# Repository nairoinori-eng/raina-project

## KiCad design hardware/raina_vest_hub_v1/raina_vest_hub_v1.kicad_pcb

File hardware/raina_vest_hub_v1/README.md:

# RAINA 背心中转控制板 v1.0（不推荐下单）

> 重要：v1 的 Arduino Nano 直插封装来自手写坐标，导入嘉立创EDA后存在封装和引脚可靠性风险。不要直接用 v1 下单。
>
> 推荐改用 `hardware/raina_vest_hub_v2_terminal`：Arduino Nano 不直接插板，而是通过 8P 线连接到中转板，PCB 上只保留传感器分压和马达驱动，风险更低。

这是一块用于替代面包板的 Arduino Nano 扩展 PCB 方案。目标是把电阻、三极管、接口全部固定到一块小板上，背心内只保留 FSR 压力传感器、振动马达和延长线。

## 0. 可直接打开的 PCB 文件

本目录已经包含一套 KiCad PCB 工程：

- `raina_vest_hub_v1.kicad_pro`
- `raina_vest_hub_v1.kicad_pcb`
- `raina_vest_hub_v1.easyeda.json`

使用方法：

1. 安装 KiCad。
2. 打开 `raina_vest_hub_v1.kicad_pro`。
3. 进入 PCB 编辑器检查板子。
4. 核对 S9012 实物脚位、Arduino Nano 插入方向、JST 插座方向。
5. 没问题后导出 Gerber，再上传嘉立创打样。

注意：这版是为了毕业设计快速落地做的手工布线小板，不是工业量产板。下单前必须人工检查 DRC，尤其是 S9012 脚位。

Nano 插座按 USB 朝上校准：

- A0/A1/A2/A3 在左排第 4/5/6/7 脚。
- 5V 在左排第 12 脚。
- GND 在左排第 14 脚。
- D5 在右排第 8 脚。
- D6 在右排第 9 脚。

如果你导入后看到 D5/D6 不在这两个位置，不要下单。

如果你使用嘉立创EDA标准版，可以直接导入 `raina_vest_hub_v1.easyeda.json`：

1. 打开嘉立创EDA标准版。
2. 选择“文件 / 导入 / EasyEDA 文件”。
3. 选择 `raina_vest_hub_v1.easyeda.json`。
4. 打开后先运行 DRC，再检查接口方向和 S9012 脚位。

## 1. 默认假设

- 主控：Arduino Nano，使用排针插到 PCB 上。
- 传感器接口：JST-XH 2P，间距 2.54mm。
- 马达接口：JST-XH 2P，间距 2.54mm。
- 电阻：直插 1/4W，间距 7.62mm。
- 三极管：S9012，TO-92 封装。
- 二极管：1N4148 / 1N4007 / 1N5819 均可，预留焊盘，正式展出建议焊上。
- PCB：2 层板，1.6mm 厚，FR-4。

## 2. 板上接口

| 接口 | 连接对象 | Arduino 引脚 | 说明 |
|---|---|---|---|
| J1 S1 | 左胸 FSR | A0 | 2P，1脚 5V，2脚信号 |
| J2 S2 | 右胸 FSR | A1 | 2P，1脚 5V，2脚信号 |
| J3 S3 | 左腰 FSR | A2 | 2P，1脚 5V，2脚信号 |
| J4 S4 | 右腰 FSR | A3 | 2P，1脚 5V，2脚信号 |
| J5 M1 | 左胸马达 | D5 | 2P，1脚马达正极，2脚 GND |
| J6 M2 | 右腰马达 | D6 | 2P，1脚马达正极，2脚 GND |

## 3. FSR 传感器电路

每一路都是同样结构：

```text
5V -> FSR -> A0/A1/A2/A3
              |
             10K
              |
             GND
```

PCB 上只放 10K 下拉电阻，FSR 本体通过 JST 线接到背心内部。

## 4. 马达驱动电路

每一路都是 S9012 高边驱动：

```text
D5/D6 -> 1K -> S9012 B
S9012 B -> 10K -> 5V
S9012 E -> 5V
S9012 C -> 马达正极
马达负极 -> GND
```

固件逻辑保持不变：Arduino 输出 LOW 时马达导通，输出 HIGH 时马达关闭。

二极管建议焊在马达两端：

```text
二极管阴极 -> 马达正极
二极管阳极 -> GND
```

## 5. 推荐 PCB 布局

参考 `raina_vest_hub_v1_top_view.svg`。

- Arduino Nano 放中间。
- 左侧放 S1-S4 四个传感器接口。
- 右侧放 M1-M2 两个马达接口。
- 每个接口旁边必须放丝印，避免背心安装时插反。
- 板子四角加 3mm 固定孔，用扎带或螺丝固定到背心外侧小盒子里。

## 6. 嘉立创EDA绘制步骤

1. 新建 2 层 PCB 工程。
2. 放置 Arduino Nano 模块插座，可以用 2 条 15P 排母代替。
3. 放置 6 个 JST-XH-2P 接口。
4. 放置 4 个 10K 下拉电阻，分别连接 A0/A1/A2/A3 到 GND。
5. 放置 2 个 S9012 TO-92、2 个 1K 电阻、2 个 10K 上拉电阻。
6. 每路马达旁预留 1 个二极管焊盘。
7. 按 `netlist.csv` 连线。
8. 铺铜：顶层和底层都铺 GND。
9. 走线建议：5V 和马达线宽 0.5mm 以上，信号线 0.25mm 以上。
10. 下单前用 DRC 检查短路和未连线。

## 7. 背心接线

背心内部每个模块做 JST 2P 插头：

```text
S1 -> J1
S2 -> J2
S3 -> J3
S4 -> J4
M1 -> J5
M2 -> J6
```

线材建议：

- FSR：28AWG 硅胶软线。
- 马达：26AWG 硅胶软线。
- 每根线 60cm 到 100cm，根据背心走线实际裁剪。

## 8. 下单前必须人工确认

- S9012 管脚顺序必须按你手里的实物确认，不同厂家可能不是同一脚位。
- JST 接口 1 脚方向要和线束一致。
- Arduino Nano 排针方向要留出 USB 插头空间。
- 如果马达供电仍用 5V，正式展出前要确认马达不明显发热。

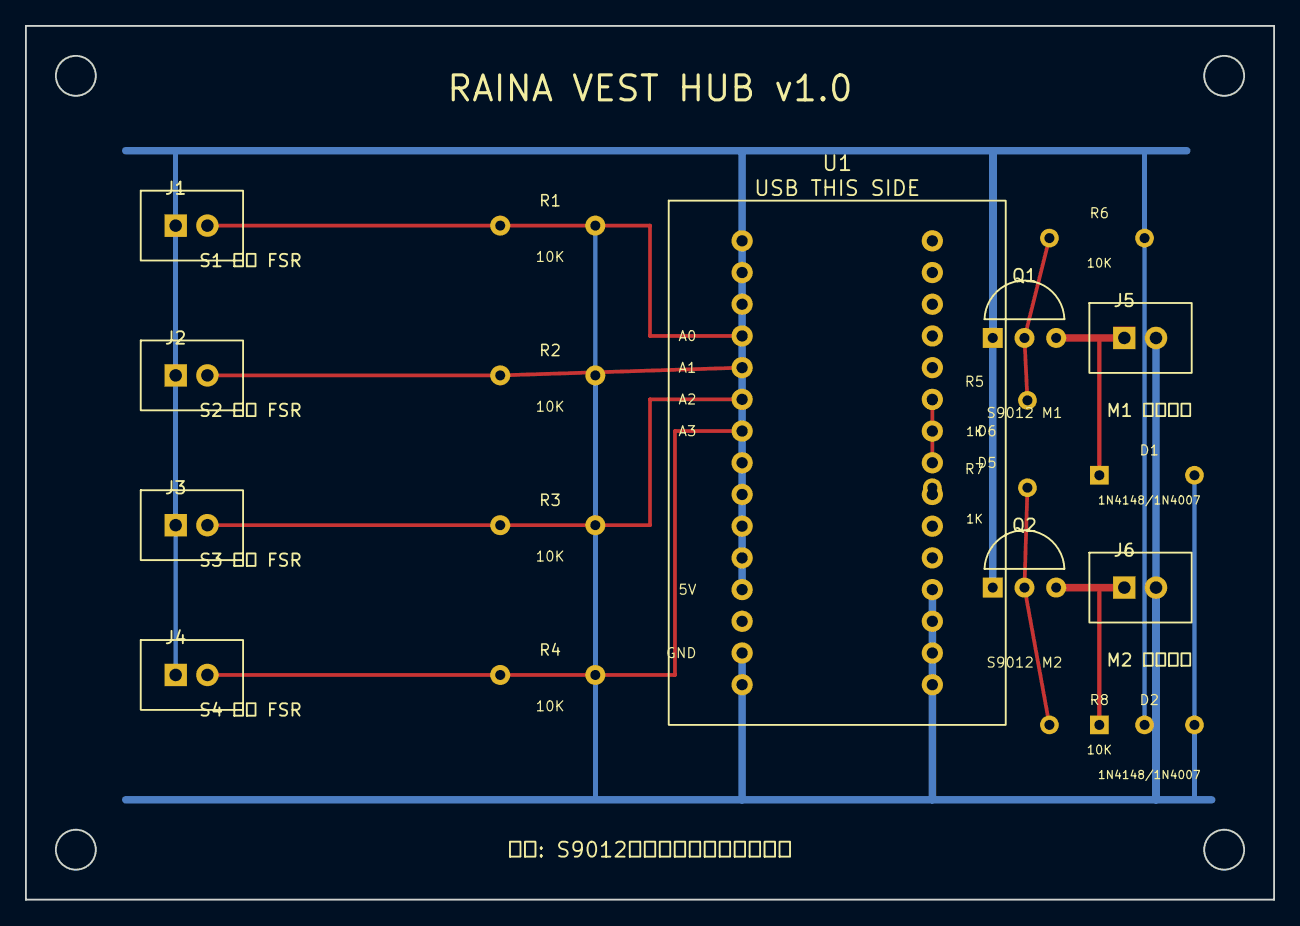
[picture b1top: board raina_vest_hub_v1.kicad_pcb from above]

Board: 2 copper layers, 100.0 x 70.0 mm, 19 parts (0 on the bottom side), 12 nets.

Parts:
D1: 1N4148/1N4007; Diode_D1
D2: 1N4148/1N4007; Diode_D2
J1: S1 左胸 FSR; JST_XH_2P_S1
J2: S2 右胸 FSR; JST_XH_2P_S2
J3: S3 左腰 FSR; JST_XH_2P_S3
J4: S4 右腰 FSR; JST_XH_2P_S4
J5: M1 左胸马达; JST_XH_2P_M1
J6: M2 右腰马达; JST_XH_2P_M2
Q1: S9012 M1; S9012_TO92_Q1
Q2: S9012 M2; S9012_TO92_Q2
R1, R2, R3, R4: 10K; Resistor_THT
R5: 1K; Resistor_R5
R6: 10K; Resistor_R6
R7: 1K; Resistor_R7
R8: 10K; Resistor_R8
U1: Arduino Nano Socket; Arduino_Nano_Socket

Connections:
+5V: J1.1, J2.1, J3.1, J4.1, Q1.E, Q2.E, R6.2, R8.2, U1.L12
GND: D1.A, D2.A, J5.2, J6.2, R1.2, R2.2, R3.2, R4.2, U1.L14, U1.R12
M1_BASE: Q1.B, R5.2, R6.1
M1_CTRL: R5.1, U1.R8
M1_POS: D1.K, J5.1, Q1.C
M2_BASE: Q2.B, R7.2, R8.1
M2_CTRL: R7.1, U1.R9
M2_POS: D2.K, J6.1, Q2.C
S1_SIG: J1.2, R1.1, U1.L4
S2_SIG: J2.2, R2.1, U1.L5
S3_SIG: J3.2, R3.1, U1.L6
S4_SIG: J4.2, R4.1, U1.L7

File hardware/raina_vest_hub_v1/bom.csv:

位号,名称,规格,封装/建议,数量,备注
U1,Arduino Nano 插座,Nano 3.0,2x15P 排母,1,Nano 插在板上
J1-J6,JST 2P 插座,JST-XH 2.54mm 2P,直插,6,S1-S4 和 M1-M2
R1-R4,电阻,10K,直插 1/4W,4,FSR 下拉
R5 R7,电阻,1K,直插 1/4W,2,S9012 基极限流
R6 R8,电阻,10K,直插 1/4W,2,S9012 基极上拉
Q1 Q2,PNP 三极管,S9012 / SS9012,TO-92,2,注意确认脚位
D1 D2,二极管,1N4148/1N4007/1N5819,直插,2,马达保护，建议焊
H1-H4,固定孔,M3,3.2mm 孔,4,固定到外壳或背心

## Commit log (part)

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2026-04-09 fix: 大幅提高藤蔓可见度（alpha/size翻倍，展宽收窄）
    - 主藤alpha: 0.40→0.75, size: 0.028→0.055
    - 径向展宽收窄（0.038→0.022），粒子更集中更实
    - shader基础亮度 0.6→0.8
    - 叶片粒子同步增强
    https://claude.ai/code/session_01WybZpkk4Z2YxGfBpvDxzQV
2026-04-09 feat: 分支藤蔓重写 — 8根手工定义路径，1:1复刻参考图
    逐根追踪参考图中的分支走势，每根用独立CatmullRom曲线：
    1. 顶部左上弯曲延伸
    2. 上部右侧短弧
    3. 左侧长S弧（箭头1位置）
    4. 右侧长S弧（箭头2位置）
    5. 中部左侧中等弧
2026-04-09 chore: 后台agent生成的解析脚本和数据
2026-04-10 feat: 用Figma路径替换正弦藤蔓系统
    - import VINE1_SEGMENTS(15段) 和 VINE2_SEGMENTS(31段) 路径数据
    - CatmullRom插值 + 弧长均匀采样，自动平滑尖锐转折
    - 拓扑分析自动检测主干/分支/末梢，主干粗分支渐细
    - 双态映射：Figma=直立态，curved=加脊柱x偏移
    - Z深度正弦缠绕 + depthFade=0.15 后方变暗
    - 颜色立体感：Z前方偏暖highlight，后方偏冷accent2
2026-04-10 fix: X缩放收回2.0，太宽了
    https://claude.ai/code/session_01WirnFCTP82t9Ja9fGtK8dX
2026-04-10 fix: 点缀藤蔓粒子大幅加密
    9000/7000/5000粒子，宽度和透明度也提升，看得清。
    https://claude.ai/code/session_01WirnFCTP82t9Ja9fGtK8dX
2026-04-10 fix: 脉冲提速/分支更细/摇曳加大/颜色渐变
    1. 脉冲速度 0.07→0.13，间隔 2.0→1.6
    2. 分支宽度 0.012→0.007，更精细
    3. 摇曳幅度 0.06→0.10，加Y微摆，慢摆+快颤双层
    4. 颜色渐变：顶部→高光暖玉色，底部→深青冷调
    Z深度也叠加微弱偏移
    https://claude.ai/code/session_01WirnFCTP82t9Ja9fGtK8dX
2026-04-10 fix: 弥散粒子加大加密加长
    每处350→800颗，尺寸0.028→0.050，alpha 0.55→0.80
    弥散距离也加长，应该清晰可见了。
    https://claude.ai/code/session_01WirnFCTP82t9Ja9fGtK8dX
2026-04-10 fix: 弥散粒子重做——沿分支曲线逐渐化开
    完全重写弥散系统：不再是单点发射，而是整个分支逐渐散开。
    - rawT 0~1: 沿分支CatmullRom曲线采样
    - rawT 1~3: 超出尖端，沿切线延伸
    - 散布宽度：根部0.003(紧凑) → 尖端渐宽 → 远处(rawT-0.4)²*0.06(很散)
    - Alpha：根部0.70(实) → 尖端半透明 → 远处渐隐消失
    - 去掉vineId=10特殊shader分支，全部用vineId=0正常渲染
2026-04-10 fix: 弥散从尖端就开始往外弯，不再只在远处
    lateralDrift改为linear+quadratic: beyond*0.25+beyond²*0.08
    一出尖端就明显往左/右弯。前进量减少(0.3x)，主要横向飘。
    https://claude.ai/code/session_01WirnFCTP82t9Ja9fGtK8dX
2026-04-10 fix: visible IDLE particles, serif fonts, no line breaks in subtitles
    1. Increased scattered particle size (0.030-0.065) and alpha (0.15-0.35)
    so they're actually visible as floating dust in IDLE state
    2. Changed all fonts to serif (Noto Serif SC / Songti SC)
    3. Removed all \n from subtitle text schedule, set white-space: nowrap
    https://claude.ai/code/session_015pu3dzf1xxgpcqjk6RX3fg
2026-04-10 fix: ambient stars 6000, much brighter and larger
    https://claude.ai/code/session_015pu3dzf1xxgpcqjk6RX3fg
2026-04-11 fix: subtitle left-aligned fixed position + peak-only segment highlight + centerline comparison
    1. Subtitles: all narrative subtitles now share the same fixed position
    (top 48%, left 7%, left-aligned), appearing one after another instead
    of jumping to different positions. Only countdown overrides to center.
    2. Segment highlight: only the curved peaks are colored now
    - thoracic peak @ t ≈ 0.33 (T7) → warm orange
    - lumbar peak @ t ≈ 0.75 (L3) → cyan
2026-04-11 Fix MCU test help output
2026-04-11 Add MCU show firmware simulator
2026-04-11 Start show experience with prepulses
2026-04-11 fix: 减少小叶数量，偏向中大
    0.05-0.22 Math.pow(r,1.6)→ 0.09-0.24 Math.pow(r,0.85)
    小叶最小提到0.08，分布偏向中大尺寸
    https://claude.ai/code/session_01WirnFCTP82t9Ja9fGtK8dX
2026-04-11 fix: Y密度限制 + 粒子数随大小 + 加强卷曲
    1. 同一y高度±0.18内超过3片的跳过
    2. 粒子数按大小线性：0.08→500颗, 0.24→1400颗
    3. 卷曲强度 ±0.12 → ±0.30
    https://claude.ai/code/session_01WirnFCTP82t9Ja9fGtK8dX
2026-04-11 fix: 弥散分支叶子收缩到尖端附近(0.05-0.20)避免飘离
    https://claude.ai/code/session_01WirnFCTP82t9Ja9fGtK8dX
2026-04-11 fix: 角度夹紧朝外 + 去掉弥散叶子 + 补充右侧辅藤A叶子
    1. 叶尖角度严格夹紧：右侧[-π/2,-0.05], 左侧[-π+0.05,-π/2]
    不会有朝内或朝上的叶子
    2. 弥散分支不放叶子（sway相位随机会脱离）
    3. 辅藤A t=0.15, 0.55（右侧）各加1片
    https://claude.ai/code/session_01WirnFCTP82t9Ja9fGtK8dX
2026-04-11 Separate prepulse cue from breathing cycle
2026-04-11 fix: 骨骼对比色大幅减少，更高级点云质感
    暖/冷对比色：10%/8% → 3%/3%
    强高光：10% → 6%
    alpha 倍数 3.5x → 2.2x，1.8x
    正常粒子占比 72% → 88%
    https://claude.ai/code/session_01WirnFCTP82t9Ja9fGtK8dX
2026-04-11 Raise default sensor threshold
2026-04-11 feat(colors): 三档饱和配色（A/MID/B），中间过渡不再灰
    用户观察：过渡段是观众看最久的阶段，要每一档都有色相。
    - 骨骼 MID 档：灰紫 → 粉红系（COLOR 粉、HL 亮粉、AC1 玫红、AC2 珊瑚玫）
    - 藤蔓新增 MID 4 色：翠绿系（粉红的对比色），同时压低 A/B 高光亮度
    - 叶子新增 MID 4 色：嫩翠系，AC1/AC2 改为跳色（A=橘红/焦糖，B=翡翠/夜紫）打破单一感
    - 新增 lerpMid 工具函数，animate 循环改用 piecewise 三段插值
    效果：
2026-04-12 feat: sync bone shape + palette + precision from claude/leaf-system
    Synced changes:
    - TUBE_Y_SCALE 1.0 → 1.9 (Z-axis elliptical cross section)
    - Vertebral disc gz formula: sin(vAngle)*vr → sin(vAngle)*vr*1.9
    - Color palette: COLOR_DARK/MID/GOLD, HL_DARK/MID/GOLD, AC1_MID, AC2_MID
    all updated to match leaf-system saturated palette
    - renderer.setPixelRatio(3.0) + uAlphaBoost compensation (pow(3/1.5,2)=4)
2026-04-12 fix(vine): 主藤加深 Z 缠绕 + 收细粒子，改善遮挡关系
    主藤 wrapR 0.06 → 0.14（Z 范围 ±0.068 → ±0.15），
    能明显穿过骨骼前后，遮挡 smoothstep 能正常触发。
    主干粒子收细：depth 0/1/2 从 0.038/0.030/0.022 → 0.028/0.022/0.016，
    与辅藤（0.022~0.028）更协调。
    https://claude.ai/code/session_01WirnFCTP82t9Ja9fGtK8dX
2026-04-12 tweak: 主藤紫色/粉色阶段 HL 再压暗
    VINE_A_HL 0x5a4628 → 0x382818（约 60%）
    VINE_MID_HL 0x2a4438 → 0x1a2e24（约 60%）
    https://claude.ai/code/session_01WirnFCTP82t9Ja9fGtK8dX
2026-04-12 fix: 花朵 3 态形状差异化（角度变化而非缩放）
    花苞：花瓣竖直向上包裹成窄高水滴（宽高比 0.64）
    半开：外层瓣翻折 65%，内层仍竖直，杯状
    全开：花瓣完全径向铺开（宽高比 ~1.0）
    https://claude.ai/code/session_01MuBKyJ2TaspmcKBSVr1t3q
2026-04-12 fix: 照参考图重写花朵形状——全圆盘采样 + 椭圆区域变换
    花苞：外层两瓣占蛋形左右半，中层上部，内层顶尖（蛋形轮廓）
    半开：外瓣展开 + 中瓣螺旋偏移 + 内瓣紧卷（玫瑰螺旋）
    全开：5 个近圆花瓣，中心距 0.28，半径 0.24（自然重叠无空隙）
    https://claude.ai/code/session_01MuBKyJ2TaspmcKBSVr1t3q
2026-04-12 wip: 花朵系统改进（两阶段动画 + 渐变 + 层次 + 跳过引导）
    - 两阶段动画：花苞出现(0.46~0.55) → 绽放(0.60~1.00)
    - 花瓣径向渐变：根部深 → 尖端亮
    - 花瓣层次：外层暗/内层亮/花蕊最亮
    - 碗形 Z 加深（0.25），Y旋转 25~50°
    - 花朵颜色提亮（additive blending 可见）
    - 跳过引导按钮
2026-04-12 Add guide skip control
2026-04-12 Clear vine and leaf visuals on reset
2026-04-16 feat: 引导进度控制 + 速度倍率（默认 3x 快进）
    - 调试面板新增引导进度滑块（拖动直接跳到指定秒数）
    - 引导速度滑块（1x~10x，默认 3x 快进文字展示）
    - 松手后从当前位置继续自动播放
    - 进度条实时同步显示
    https://claude.ai/code/session_01MuBKyJ2TaspmcKBSVr1t3q
2026-04-28 Add show launcher and guard experience state
2026-04-30 feat: 花朵去掉花苞，直接全开态逐瓣显现
    - 删除 bud/half morphing，只用 bloomPos
    - 花蕊先出 → 瓣0→瓣1→...→瓣4 依次渐入
    - 每瓣内部从花心向外渐进显现（渗透效果）
    - 新增 aPetalIdx + aDistFromCenter 属性驱动
    - 删除两阶段 bloom 动画，简化为单阶段 grow
    https://claude.ai/code/session_01MuBKyJ2TaspmcKBSVr1t3q
2026-04-30 tweak: 叶子描边加强（alpha 0.90+, size 0.030+）
    边缘粒子更亮更大，填充粒子压暗，对比更强
    https://claude.ai/code/session_01MuBKyJ2TaspmcKBSVr1t3q
2026-04-30 tweak: 藤蔓外扩加大（0.35→0.60）
    https://claude.ai/code/session_01MuBKyJ2TaspmcKBSVr1t3q
2026-04-30 fix: 花朵高度渐变加大色相差（暖杏黄→淡粉→冷蓝灰）
    色板拉开：HL=暖杏黄, AC1=淡玫粉, AC2=淡蓝灰
    高度 CV 范围加大到 +0.6 ~ -0.70，顶部明显偏暖黄，底部明显偏冷蓝
    https://claude.ai/code/session_01MuBKyJ2TaspmcKBSVr1t3q
2026-04-30 tweak: 花数量减少（40%→30%）
    https://claude.ai/code/session_01MuBKyJ2TaspmcKBSVr1t3q
2026-04-30 tweak: 骨骼粒子减量+结构密集填充稀疏
    N_BONE 80000→60000，内部填充比 25%→15%
    内部粒子 alpha/size 压低，管壁结构更突出
    https://claude.ai/code/session_01MuBKyJ2TaspmcKBSVr1t3q
2026-05-01 feat: 添加 BGM 背景音乐 + 右下角播放控制按钮
    - index.html: 加 audio 元素（loop, preload）+ 右下角圆形 toggle 按钮（SVG 扬声器+三角/声波两态切换）+ 调试面板音量滑块
    - style.css: bgm-toggle 圆形半透明样式，hover 加亮，播放时三道声波依次淡入淡出
    - app.js: 点击 toggle play/pause，监听 audio play/pause 事件同步 .playing class，音量滑块绑定 audio.volume
    - 默认音量 50%，进页面默认暂停（首次点击同时绕过 autoplay 限制）
2026-05-01 chore: 删除废弃的 spine-viz/main.js + 修正 CLAUDE.md 主文件引用
    main.js 是 app.js 的旧拷贝（90KB），index.html 实际加载的是 app.js。
    删除避免后续误导。同步：
    - CLAUDE.md 主文件改成 app.js
    - CLAUDE.md 开发分支字段改成 main（旧的 add-capabilities-docs-CdrcV 已不存在）
    - index.html 注释里的 main.js 改成 app.js
    https://claude.ai/code/session_014JFGfo1gbemwmYymoHDcc8
2026-05-01 feat(guide): 节拍器粒子球重做（密度/震荡/拖尾参考用户图）
    从 144 → 2500 粒子，分两类填满圆盘：
    - 核心粒子 70%：sqrt 分布按面积均匀填满圆盘（含中心）
    - 尖刺粒子 30%：边缘附近，吸气时径向延伸 + 自带脉动拖尾
    视觉技巧：
    - 高频径向震荡（边缘更明显）→ 震荡感
    - 尖刺粒子延伸 + 拖尾位移 → 吸气时外飞拖尾
2026-05-02 fix(guide): 凝聚后停 1s 再上字 + 28/18 度锚定 + 中轴线闪烁修复 + 波次更分明
    任务 1：粒子凝聚后留白 1s 再开始段 1
    - TEXT_SCHEDULE 全部 +1s
    - updateGuide 阶段边界 +1s
    - 总时长 82s → 83s
    任务 2：脊柱中轴线闪烁修复
    - 弥散流（diffuseMat / Layer C）在 IDLE 和 GUIDE 都隐藏
2026-05-03 revert(trail): 删除拖尾粒子系统（性能问题）
    完全移除：
    - 独立的 trailGeo / trailMat / trailPoints 粒子系统
    - aTrailFlag / aTailIdx attribute
    - vTrailBoost varying（spine vertex/fragment shader）
    - updateGuide / enterExperience / resetToIdle 中的 trailMat 同步
    - N_TAIL_SAMPLES / trailIndicesArr / 所有 tl* arrays
2026-05-04 feat(render): 渲染管线第一步 — 启用 ACESFilmic + bloom 拉强
    - renderer 加 ACESFilmicToneMapping + outputColorSpace SRGB
    - bloom strength 0.15 → 0.35, radius 0.15 → 0.3, threshold 0.45 → 0.35
    - bloom 分辨率 0.5x → 0.75x（不糊）
    - userBloomStrength 默认值 0.12 → 0.32，HTML slider 同步更新
    - shader clamp 暂保留（HDR 颜色留给第二步）
2026-05-04 fix(guide): 凝聚保持紫色 + 变弯加快到 3s
    - 凝聚阶段不再变金色（跟 IDLE 紫色一致，避免突兀）
    - 颜色全程保持紫色（DARK 系），段 3 微暖色温由段内逻辑覆盖
    - 变弯时长 4s → 3s（5~8s 变弯，剩 1.5s 等"统计说"出现）
    - 形态变化（直→弯）保持，仅取消颜色变化
2026-05-04 feat(audio): 拆吸气/呼气独立文件，严格对齐视觉 8s 周期
    时间表：
    - t=0 吸气 inhale.mp3 (3s 长)
    - t=3 静音 1s
    - t=4 呼气 exhale.mp3 (3s 长)
    - t=7 静音 1s
    - t=8 下一轮
2026-05-04 fix(experience): 呼吸文字回到左侧字幕处 + 透明度 0.9 → 0.65（更克制）
2026-05-05 feat(rib): 凹侧改成反扇形漏斗（远端 Y 聚拢）
    之前凹侧 archDown 0.25~0.35（跨度 0.10）→ 6 根肋骨几乎平行
    改成 mix(0.85, 0.20)（最上陡下→最下缓）→ 远端 Y 聚拢到中间区域
    凹侧 archUp 也对应反向：mix(0.10, 0.40)（最上低→最下高）
    形成"漏斗对称"形态：
    - 最上肋骨陡下伸展（archDown 0.85, archUp 0.10）
    - 最下肋骨高拱缓下（archDown 0.20, archUp 0.40）
2026-05-05 feat(palette): 颜色架构重做 — 5 区间纯色选择，阶段一应用
    新架构：
    - shader 改成按 vColorVar 分 5 区间直接选纯色（不 mix）
    - 每个 mat 用 uniform vec3 uPalette[5] 装色板
    - 不再 mix 出中间色，每个粒子显示明确颜色
    阶段一 Indigo × Amber 颜色应用到 7 个 mat：
    spineMat: [11193A, 11193A, 42306D, 42306D, B98B58]
2026-05-05 fix(palette): rebalance spine gold and violet
2026-05-05 fix(palette): shape base gold along spine edge
2026-05-05 fix(palette): 阶段二粉紫加强 + 浅蓝降亮
    - palette[6] #A867A0 → #B855B0 (饱和 32% → 45%)
    - palette[3] #A8C8D8 → #7CAFC8 (明度 75% → 60%, 不再过曝)
    - sidePink 触发概率 0.72 → 0.82, alpha 1.28/1.30 → 1.55
2026-05-05 fix(palette): 阶段三金色独占区域，避免和蓝色叠加发绿
    - palette[3]/[6] #C19A30 → #C68A3E 调回原色
    - Layer A sin-mask 外层区: 100% 走金/olive，不再混入蓝色基底
    - Layer B 椎丸 outer ring + 角度通过区: 100% 走金/olive
    金色独立成团，跟主体冰蓝物理隔开，加性混合不再发绿
2026-05-05 fix(vine): 弥散粒子衔接主藤，消除接缝突变
    根部 rawT<0.3~0.5 范围内继承主藤的颜色渐变、Z 正弦缠绕、宽度，
    平滑过渡到远端的冷紫飘散，避免视觉断层。
2026-05-05 fix(vine): drift 根部 spread 改成 0.012，和主藤同宽
2026-05-05 fix(vine): 恢复 DRIFT_SEG_INDICES 用于主藤循环跳过 + 删 driftEmitters 死代码
2026-05-06 fix(vine): 平滑配色过渡 + 辅藤渐变 + 脉冲压暗 + drift 分区平滑
    1) 主藤 6 段 vColorVar 用线性插值替代硬切换，相邻段平滑过渡
    2) 辅藤复用同款 6 段 band 渐变（不再固定 lavender）
    3) 脉冲 alpha/size 压暗：主藤 0.08→0.05，辅藤 0.45/0.5→0.20/0.25
    4) drift 分区平滑：紫(0~0.5) → 紫蓝过渡(0.5~1.0) → 蓝(1.0~2.5) → 蓝+金 mix(>2.5)
2026-05-06 feat(vine): 三阶段独立 palette + drift 按"侧+阶段"组合烘焙色相
    - 新增 vineFragmentShader：5 段 PICK_COLOR_VINE × 3 阶段加权混合
    - vineMat 用 uPaletteP1/P2/P3 替代单一 uPalette
    - aColorVarTriple (vec3) 替代 aColorVar，每粒子带三阶段独立色
    - 三阶段 vine palette：
    - P1 (现状): 深蓝/紫/淡紫/淡金/淡金高光
    - P2 (粉紫·蓝·橄榄·米白): 粉紫(0xA867A0)/蓝(0x3A5A95)/淡紫蓝/橄榄(0x82A85F)/米白(0xE8DCC2)
2026-05-06 fix(leaf): 恢复叶子整体飘动（不依赖 yInLeaf，所有粒子同步偏移=不形变）
2026-05-06 fix(leaf): 叶子朝向改成沿藤蔓法线扇形朝外（不再强制下垂）
    之前 centerWorldAngle 被写死成右侧 -50° / 左侧 -130°，所有叶子都朝下垂。
    现在直接用 (leafOutX, leafOutY) 的真实世界角度作为基准（=垂直于
    藤蔓切线的外法线），加 ±π*0.14 随机散射 + 簇内偏移，叶子自然按所在
    藤段法线方向扇形朝外，整体姿态从下垂变成横向伸展。
2026-05-06 fix(flower): 描边更实（alpha 拉到接近 1 + 描边粒子占比 35%→55%）
    按叶子描边逻辑（线条粒子靠密度形成实感）：
    - flower-shapes.js: EDGE_RATIO 0.35 → 0.55，每瓣描边粒子翻倍
    - app.js: 描边 alpha 0.75-0.90 → 0.96-1.00（接近不透明）
    - 花蕊 alpha 0.90 → 0.92
2026-05-06 feat: 9 项调整（IDLE 配色 + 高亮色 + 肋骨生长 + 文字驻留 + 呼吸幅度 + 镜头 + 衔接 + bgm）
    #1 IDLE 悬浮粒子加色变化：ambCVars 散布到 -0.95~+0.95，
    ambMat palette 改 5 色（深蓝/紫/深紫/暗金/银蓝高光）替代单色暗紫
    #2 GUIDE 数字高亮：hl-warm 调和成淡金 0xD8B878；新增 hl-cool 0xB8A6D6
    腰椎左凸用冷紫，胸椎右凸用暖金（脊柱 P1 调色板内取色）
    #3 肋骨生长动画：ribMat 加 uGrowth uniform，按 aPathT 生长遮罩；
    动画循环里 22.5~24.5s 内 uGrowth 0→1 推进
